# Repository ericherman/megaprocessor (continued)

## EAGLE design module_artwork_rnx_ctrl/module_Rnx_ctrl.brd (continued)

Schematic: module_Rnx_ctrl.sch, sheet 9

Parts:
CMP26, CMP27: 2OR
CMP28: 3AND
CMP29, CMP30: 3OR
CMP48, CMP49: 1BUF

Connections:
ADDER_X_MUX_R0: CMP26.OUT_P, CMP30.P$1 (0); also elsewhere on the board
ADDER_X_MUX_R1: CMP27.OUT_P, CMP30.P$2 (1); also elsewhere on the board
ADDER_X_MUX_R1__DIV: CMP27.P$1 (A2); also elsewhere on the board
ADDER_X_MUX_R3: CMP29.OUT_P, CMP30.P$3 (2); also elsewhere on the board
ADDER_X_MUX_R3_SET_A: CMP28.OUT_P, CMP29.P$1 (0)
ADDER_X_MUX_SPECIAL: CMP30.OUT_P; also elsewhere on the board
ADDER_X_MUX_SPECIAL_N: CMP30.OUT_M (N)
OPCODE_IS_ADDX: CMP26.P$2 (A1); also elsewhere on the board
OPCODE_IS_MUL: CMP28.P$3 (3); also elsewhere on the board
OPCODE_IS_SQRT: CMP27.P$2 (A1); also elsewhere on the board
OPCODE_IS_SUBX: CMP26.P$1 (A2); also elsewhere on the board
STATE_0: CMP48.IN; also elsewhere on the board
STATE_0_N: CMP28.P$2 (2), CMP48.N; also elsewhere on the board
STATE_11: CMP29.P$2 (1); also elsewhere on the board
STATE_13: CMP29.P$3 (2), CMP49.IN; also elsewhere on the board
STATE_13_N: CMP28.P$1 (1), CMP49.N

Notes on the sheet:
adder_x_mux_r0 = Cpnt_2OR(bus_decode_rnx_2.opcode_is_addx, bus_decode_rnx_2.opcode_is_subx);
adder_x_mux_r1 = Cpnt_2OR(bus_decode_rnx_1.opcode_is_sqrt, adder_x_mux_r1__div);
adder_x_mux_r3_A = Cpnt_3AND(bus_decode_rnx_1.opcode_is_mul, ~bus_state[0], ~bus_state[13]);
adder_x_mux_r3 = Cpnt_3OR(bus_state[11], bus_state[13],adder_x_mux_r3_A);
adder_x_special = Cpnt_3OR(adder_x_mux_r0, adder_x_mux_r1, adder_x_mux_r3);

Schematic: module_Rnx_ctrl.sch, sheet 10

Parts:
CMP32, CMP37: 2OR
CMP33, CMP34: 2AND
CMP35, CMP36: 3OR

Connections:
ADDER_X_MUX_R0: CMP35.P$1 (0); also elsewhere on the board
ADDER_X_MUX_R1: CMP36.P$1 (0); also elsewhere on the board
ADDER_X_MUX_R3: CMP37.P$1 (A2); also elsewhere on the board
ADDER_X_MUX_SPECIAL: CMP32.P$1 (A2); also elsewhere on the board
INSTR_0: CMP34.P$1 (1); also elsewhere on the board
INSTR_0_N: CMP33.P$1 (1); also elsewhere on the board
OPCODE_IS_INDIRECT_POSTINC: CMP32.P$2 (A1), CMP33.P$2 (2), CMP34.P$2 (2); also elsewhere on the board
RAC_MUX_0: CMP35.OUT_P; also elsewhere on the board
RAC_MUX_1: CMP36.OUT_P; also elsewhere on the board
RAC_MUX_3: CMP37.OUT_P; also elsewhere on the board
RA_MUX_0_RC: CMP33.OUT_P, CMP35.P$2 (1)
RA_MUX_1_RC: CMP34.OUT_P, CMP36.P$2 (1)
RA_MUX_NORM_EN: CMP32.OUT_M (N); also elsewhere on the board
RA_NORM_0: CMP35.P$3 (2); also elsewhere on the board
RA_NORM_1: CMP36.P$3 (2); also elsewhere on the board
RA_NORM_3: CMP37.P$2 (A1); also elsewhere on the board

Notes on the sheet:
RAC_mux_0 = Cpnt_3OR(adder_x_mux_r0, RA_mux_0__norm, RA_mux_0__RC);
RAC_mux_1 = Cpnt_3OR(adder_x_mux_r1, RA_mux_1__norm, RA_mux_1__RC);
RAC_mux_2 = RA_mux_2__norm;
RAC_mux_3 = Cpnt_2OR(adder_x_mux_r3, RA_mux_3__norm);
RA_mux_0__RC = Cpnt_2AND(bus_decode_rnx_2.opcode_is_indirect_postinc, ~RC_bit);
RA_mux_1__RC = Cpnt_2AND(bus_decode_rnx_2.opcode_is_indirect_postinc, RC_bit);
RA_mux_norm_en = ~Cpnt_2OR(adder_x_special, bus_decode_rnx_2.opcode_is_indirect_postinc);

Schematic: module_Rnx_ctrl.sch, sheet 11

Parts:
CMP20, CMP80: 2X2AND_OR
CMP22: 2AND
CMP82: 5OR

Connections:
INSTR_7_N: CMP22.P$1 (1); also elsewhere on the board
OPCODE_IS_LDI_X: CMP20.P$2 (A1), CMP20.P$3 (B0); also elsewhere on the board
OPCODE_IS_LD_ST: CMP80.P$1 (A0), CMP80.P$3 (B0); also elsewhere on the board
SHIFT_IS_SHIFTING: CMP82.3 (2); also elsewhere on the board
STATE_0: CMP20.P$4 (B1); also elsewhere on the board
STATE_1: CMP20.P$1 (A0); also elsewhere on the board
STATE_4: CMP80.P$4 (B1); also elsewhere on the board
STATE_5: CMP80.P$2 (A1); also elsewhere on the board
WR_RN_USING_RAC: CMP82.OUT_P; also elsewhere on the board
WR_RN_USING_RAC__MEM: CMP80.OUT_P, CMP82.4 (3)
WR_RN_USING_RA__BIT: CMP82.2 (1); also elsewhere on the board
WR_RN_USING_RA__LDI: CMP20.OUT_P, CMP82.1 (0)
WR_RN_USING_RA__REG_REG: CMP22.OUT_P, CMP82.5 (4)
WR_RN_USING_RA__REG_REG_EXCEPTIONS_N: CMP22.P$2 (2); also elsewhere on the board

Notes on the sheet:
wr_RN_using_ra__ldi = Cpnt_2x2AND_OR( bus_state[0], bus_decode_rnx_1.opcode_is_ldi_x, bus_state[1], bus_decode_rnx_1.opcode_is_ldi_x);
wr_RN_using_ra__reg_reg = Cpnt_2AND(is_simple_reg_to_reg, bus_decode_rnx_1.wr_RN_using_ra__reg_reg_exceptions_n);
wr_RN_using_rac__mem = Cpnt_2x2AND_OR(bus_state[4], bus_decode_rnx_1.opcode_is_ld_st, bus_state[5], bus_decode_rnx_1.opcode_is_ld_st);
wr_RN_using_rac = Cpnt_5OR( wr_RN_using_ra__reg_reg, wr_RN_using_rac__mem, bus_decode_rnx_1.wr_RN_using_ra__bit, wr_RN_using_ra__ldi, bus_decode_rnx_1.shift_is_shifting);

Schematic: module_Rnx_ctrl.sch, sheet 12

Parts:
CMP2: 2X2AND_OR
CMP3, CMP4: 4OR
CMP6, CMP7: 2OR

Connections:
ADDER_Y_MUX_R0: CMP2.OUT_P, CMP4.4 (3); also elsewhere on the board
ADDER_Y_MUX_R1: CMP3.OUT_P, CMP4.2 (1); also elsewhere on the board
ADDER_Y_MUX_R2__DIV: CMP4.1 (0); also elsewhere on the board
ADDER_Y_MUX_R3: CMP4.3 (2), CMP6.OUT_P; also elsewhere on the board
ADDER_Y_MUX_SPECIAL: CMP4.OUT_P, CMP7.P$1 (A2); also elsewhere on the board
ADDER_Y_MUX_SPECIAL_N: CMP4.OUT_M (N)
OPCODE_IS_ADDX: CMP3.1 (0); also elsewhere on the board
OPCODE_IS_DIVS_STATE_0: CMP3.3 (2); also elsewhere on the board
OPCODE_IS_MULS: CMP2.P$2 (A1); also elsewhere on the board
OPCODE_IS_NEGX: CMP2.P$3 (B0), CMP2.P$4 (B1); also elsewhere on the board
OPCODE_IS_SHIFT_BIT: CMP7.P$2 (A1); also elsewhere on the board
OPCODE_IS_SQRT: CMP6.P$2 (A1); also elsewhere on the board
OPCODE_IS_SUBX: CMP3.2 (1); also elsewhere on the board
RB_MUX_NORM_EN: CMP7.OUT_M (N); also elsewhere on the board
STATE_3: CMP2.P$1 (A0); also elsewhere on the board
STATE_11: CMP3.4 (3); also elsewhere on the board
STATE_12: CMP6.P$1 (A2); also elsewhere on the board

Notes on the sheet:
adder_y_mux_r0 = Cpnt_2x2AND_OR( bus_decode_rnx_2.opcode_is_negx, bus_decode_rnx_2.opcode_is_negx, bus_decode_rnx_2.opcode_is_muls, bus_state[3]);
adder_y_mux_r1 = Cpnt_4OR(bus_decode_rnx_2.opcode_is_addx, bus_decode_rnx_2.opcode_is_subx, adder_y_mux_r1__div, bus_state[11]);
adder_y_mux_r2 = adder_y_mux_r2__div;
adder_y_mux_r3 = Cpnt_2OR(bus_decode_rnx_1.opcode_is_sqrt, adder_y_mux_r3__div);
adder_y_special = Cpnt_4OR(adder_y_mux_r0, adder_y_mux_r1, adder_y_mux_r2, adder_y_mux_r3);
RB_mux_norm_en = ~Cpnt_2OR(adder_y_special, bus_decode_rnx_2.opcode_is_shift_bit);

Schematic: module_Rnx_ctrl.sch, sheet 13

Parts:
CMP8, CMP12, CMP14, CMP19: 3OR

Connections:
ADDER_Y_MUX_R0: CMP8.P$3 (2); also elsewhere on the board
ADDER_Y_MUX_R1: CMP12.P$2 (1); also elsewhere on the board
ADDER_Y_MUX_R2__DIV: CMP14.P$1 (0); also elsewhere on the board
ADDER_Y_MUX_R3: CMP19.P$1 (0); also elsewhere on the board
RB_MUX_0: CMP8.OUT_P; also elsewhere on the board
RB_MUX_1: CMP12.OUT_P; also elsewhere on the board
RB_MUX_2: CMP14.OUT_P; also elsewhere on the board
RB_MUX_3: CMP19.OUT_P; also elsewhere on the board
RB_NORM_0: CMP8.P$1 (0); also elsewhere on the board
RB_NORM_1: CMP12.P$1 (0); also elsewhere on the board
RB_NORM_2: CMP14.P$3 (2); also elsewhere on the board
RB_NORM_3: CMP19.P$2 (1); also elsewhere on the board
RB_SHIFT_0: CMP8.P$2 (1); also elsewhere on the board
RB_SHIFT_1: CMP12.P$3 (2); also elsewhere on the board
RB_SHIFT_2: CMP14.P$2 (1); also elsewhere on the board
RB_SHIFT_3: CMP19.P$3 (2); also elsewhere on the board

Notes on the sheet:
RB_mux_0 = Cpnt_3OR(adder_y_mux_r0, RB_mux_0__shift, RB_mux_0__norm);
RB_mux_1 = Cpnt_3OR(adder_y_mux_r1, RB_mux_1__shift, RB_mux_1__norm);
RB_mux_2 = Cpnt_3OR(adder_y_mux_r2, RB_mux_2__shift, RB_mux_2__norm);
RB_mux_3 = Cpnt_3OR(adder_y_mux_r3, RB_mux_3__shift, RB_mux_3__norm);

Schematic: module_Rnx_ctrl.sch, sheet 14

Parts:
CMP55: 1BUF
CMP58, CMP59: 2X2AND_OR
CMP60: 4AND
CMP61: 5OR
CMP85: 3AND

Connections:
ADD2_X_MUX_RI_SP__STACK_SET_A: CMP59.OUT_P
ADD2_X_MUX_RI_SP__STACK_SET_A_N: CMP59.OUT_M (N), CMP60.P$4 (3)
ADD2_X_MUX_RI__H: CMP85.OUT_P; also elsewhere on the board
ADD2_X_MUX_RI__SP: CMP61.OUT_P; also elsewhere on the board
ADD2_X_MUX_RI__SP__JSR_ABS: CMP58.OUT_P, CMP61.4 (3); also elsewhere on the board
ADD2_X_MUX_RI__SP__STACK: CMP60.OUT_P, CMP61.5 (4)
INSTR_6_N: CMP85.P$3 (3); also elsewhere on the board
INSTR_7: CMP85.P$2 (2); also elsewhere on the board
IS_END_N: CMP60.P$2 (1); also elsewhere on the board
IS_STATE_4_6: CMP85.P$1 (1); also elsewhere on the board
OPCODE_IS_ADD_SP_STATE_2: CMP61.1 (0); also elsewhere on the board
OPCODE_IS_JSR_ABS: CMP55.IN, CMP58.P$2 (A1), CMP58.P$4 (B1); also elsewhere on the board
OPCODE_IS_JSR_ABS_N: CMP55.N, CMP60.P$3 (2)
OPCODE_IS_JSR_R0: CMP59.P$4 (B1); also elsewhere on the board
OPCODE_IS_MOVE_R0_SP_STATE_0: CMP61.2 (1); also elsewhere on the board
OPCODE_IS_STACK_GROUP: CMP60.P$1 (0); also elsewhere on the board
OPCODE_IS_STACK_REL_STATE_2: CMP61.3 (2); also elsewhere on the board
OPCODE_IS_TRAP: CMP59.P$2 (A1); also elsewhere on the board
STATE_0: CMP59.P$1 (A0); also elsewhere on the board
STATE_6: CMP58.P$1 (A0); also elsewhere on the board
STATE_7: CMP59.P$3 (B0); also elsewhere on the board
STATE_15: CMP58.P$3 (B0); also elsewhere on the board

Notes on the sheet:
add2_x_mux_ri__h = Cpnt_3AND(bus_f_instr.instr[7], ~bus_f_instr.instr[6], is_state_4_6);
add2_x_mux_ri__sp__jsr_abs = Cpnt_2x2AND_OR(bus_decode_rnx_2.opcode_is_jsr_abs, bus_state[15], bus_decode_rnx_2.opcode_is_jsr_abs, bus_state[6]);
add2_x_mux_ri__sp__stack_set_A = Cpnt_2x2AND_OR(bus_decode_rnx_2.opcode_is_jsr_r0, bus_state[7], bus_state[0], bus_decode_rnx_2.opcode_is_trap);
add2_x_mux_ri__sp__stack = Cpnt_4AND(bus_decode_rnx_2.opcode_is_stack_group, bus_decode_rnx_2.is_end_n, ~bus_decode_rnx_2.opcode_is_jsr_abs, ~add2_x_mux_ri__sp__stack_set_A);
add2_x_mux_ri__sp = Cpnt_5OR(bus_decode_rnx_2.opcode_is_stack_rel_state_2, bus_decode_rnx_2.opcode_is_add_sp_state_2, bus_decode_rnx_1.opcode_is_move_r0_sp_state_0, add2_x_mux_ri__sp__stack, add2_x_mux_ri__sp__jsr_abs);

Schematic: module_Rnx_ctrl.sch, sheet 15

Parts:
CMP1, CMP41, CMP62: 2OR
CMP43: 3OR
CMP45, CMP64: 2X2AND_OR

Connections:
ADD2_X_MUX_RI__H: CMP41.P$1 (A2); also elsewhere on the board
ADD2_X_MUX_RI__SP: CMP43.P$1 (0); also elsewhere on the board
ALL_POPS: CMP64.P$2 (A1); also elsewhere on the board
INSTR_1_N: CMP45.P$2 (A1); also elsewhere on the board
IS_STATE_0_4: CMP62.OUT_P, CMP64.P$1 (A0)
NEXT_ADDR_MUX_RI__SP: CMP64.OUT_P; also elsewhere on the board
RI_MUX_2_QUAL: CMP45.OUT_P; also elsewhere on the board
RI_MUX_H: CMP41.OUT_P, CMP43.P$2 (1); also elsewhere on the board
RI_MUX_R2: CMP1.OUT_P, CMP43.P$3 (2), CMP45.P$3 (B0), CMP45.P$4 (B1)
RI_MUX_SPECIAL: CMP43.OUT_P
RI_MUX_SPECIAL_N: CMP43.OUT_M (N), CMP45.P$1 (A0); also elsewhere on the board
STATE_0: CMP62.P$1 (A2); also elsewhere on the board
STATE_4: CMP62.P$2 (A1); also elsewhere on the board
STATE_8: CMP64.P$3 (B0), CMP64.P$4 (B1); also elsewhere on the board
STATE_11: CMP1.P$1 (A2); also elsewhere on the board
STATE_12: CMP1.P$2 (A1); also elsewhere on the board
STATE_14: CMP41.P$2 (A1); also elsewhere on the board

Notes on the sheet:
is_state_0_4 = Cpnt_2OR(bus_state[0], bus_state[4]);
next_addr_mux_ri__sp_set_A = bus_decode_rnx_2.all_pops;
next_addr_mux_ri__sp = Cpnt_2x2AND_OR(bus_state[8], bus_state[8], next_addr_mux_ri__sp_set_A, is_state_0_4);
RI_mux_h = Cpnt_2OR(add2_x_mux_ri__h, bus_state[14]);
RI_mux_sp = add2_x_mux_ri__sp;// superset | next_addr_mux_ri__sp;
RI_mux_r2 = Cpnt_2OR(bus_state[11],bus_state[12]);//,bus_state[13]);
RI_mux_special = Cpnt_3OR( RI_mux_h, RI_mux_sp, RI_mux_r2);
RI_mux_2 = ~RI_bit; RI_mux_3 = RI_bit;
RI_mux_2_qual = Cpnt_2x2AND_OR(RI_mux_2, ~RI_mux_special, RI_mux_r2, RI_mux_r2);

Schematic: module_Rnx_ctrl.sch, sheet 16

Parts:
CMP5: 2X2AND_OR
CMP13: 5OR
CMP15: 2OR
CMP16, CMP17, CMP46: 2AND
CMP50: 2X3AND_OR
CMP83: 1BUF

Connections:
DIR_SZ_IS_LOAD_BYTE: CMP16.P$2 (2); also elsewhere on the board
DIR_SZ_IS_LOAD_WORD: CMP17.P$2 (2); also elsewhere on the board
INSTR_1: CMP46.P$1 (1); also elsewhere on the board
INSTR_2: CMP50.P$5 (B1); also elsewhere on the board
INSTR_2_N: CMP50.P$2 (A1); also elsewhere on the board
INSTR_7_N: CMP5.P$4 (B1); also elsewhere on the board
IS_STATE_4_6: CMP50.P$1 (A0); also elsewhere on the board
MAIN_RN_INPUT_MUX_0XT_READ: CMP15.OUT_P; also elsewhere on the board
MAIN_RN_INPUT_MUX_0XT_READ__LOAD_BYTE: CMP15.P$2 (A1), CMP16.OUT_P
MAIN_RN_INPUT_MUX_ALU: CMP13.OUT_P; also elsewhere on the board
MAIN_RN_INPUT_MUX_ALU__SET_A: CMP5.OUT_P, CMP13.5 (4)
MAIN_RN_INPUT_MUX_SHIFT_RAC: CMP17.OUT_P; also elsewhere on the board
OPCODE_IS_DIV: CMP13.3 (2); also elsewhere on the board
OPCODE_IS_LD_ST: CMP16.P$1 (1), CMP17.P$1 (1); also elsewhere on the board
OPCODE_IS_MUL: CMP5.P$2 (A1); also elsewhere on the board
OPCODE_IS_POP_PS: CMP15.P$1 (A2); also elsewhere on the board
OPCODE_IS_POSTINC_GROUP: CMP50.P$3 (A2), CMP50.P$4 (B0); also elsewhere on the board
OPCODE_IS_SHIFT_BIT: CMP13.2 (1); also elsewhere on the board
OPCODE_IS_SQRT: CMP13.1 (0); also elsewhere on the board
OPCODE_IS_SXT: CMP83.IN; also elsewhere on the board
OPCODE_IS_SXT_N: CMP5.P$3 (B0), CMP83.N
OPCODE_IS_X_ARITH: CMP13.4 (3); also elsewhere on the board
RI_MUX_3_QUAL: CMP46.OUT_P; also elsewhere on the board
RI_MUX_SPECIAL_N: CMP46.P$2 (2); also elsewhere on the board
STATE_0: CMP50.P$6 (B2); also elsewhere on the board
STATE_0_N: CMP5.P$1 (A0); also elsewhere on the board
WR_RN_USING_RI: CMP50.OUT_P; also elsewhere on the board

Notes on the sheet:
RI_mux_3_qual = Cpnt_2AND(RI_mux_3, ~RI_mux_special);
wr_RN_using_ri = Cpnt_2x3AND_OR(bus_decode_rnx_1.opcode_is_postinc_group, size_bit_is_byte, bus_state[0], bus_decode_rnx_1.opcode_is_postinc_group, ~size_bit_is_byte, is_state_4_6);
main_rn_input_mux_sxt = bus_decode_rnx_1.opcode_is_sxt;
main_rn_input_mux_alu__set_A = Cpnt_2x2AND_OR(is_simple_reg_to_reg, ~bus_decode_rnx_1.opcode_is_sxt, bus_decode_rnx_1.opcode_is_mul, ~bus_state[0]);
main_rn_input_mux_alu = Cpnt_5OR(main_rn_input_mux_alu__set_A, bus_decode_rnx_1.opcode_is_x_arith, bus_decode_rnx_2.opcode_is_shift_bit, bus_decode_rnx_1.opcode_is_sqrt, bus_decode_rnx_2.opcode_is_div);
main_rn_input_mux_0xt_read__load_byte = Cpnt_2AND(dir_sz_is_load_byte, bus_decode_rnx_1.opcode_is_ld_st);
main_rn_input_mux_0xt_read = Cpnt_2OR(main_rn_input_mux_0xt_read__load_byte, bus_decode_rnx_1.opcode_is_pop_ps);
main_rn_input_mux_shift_rac__mem_subgroup = bus_decode_rnx_1.opcode_is_ld_st;
main_rn_input_mux_shift_rac = Cpnt_2AND(dir_sz_is_load_word, main_rn_input_mux_shift_rac__mem_subgroup);

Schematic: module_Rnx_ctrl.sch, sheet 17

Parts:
CMP63, CMP74: 2OR
CMP72: 3AND
CMP91: 1BUF

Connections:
ADD1_RESULT_IS_N: CMP91.IN; also elsewhere on the board
ADD1_RESULT_IS_P: CMP63.P$1 (A2), CMP91.N
H_0: CMP72.P$2 (2); also elsewhere on the board
R1_IS_N: CMP63.P$2 (A1); also elsewhere on the board
SQRT_CONDITIONAL: CMP63.OUT_P, CMP72.P$1 (1)
SQRT_ODD_CONDITIONAL: CMP72.OUT_P, CMP74.P$2 (A1); also elsewhere on the board
SQRT_ODD_CONDITIONAL_MUL_14: CMP74.OUT_P; also elsewhere on the board
STATE_10: CMP72.P$3 (3); also elsewhere on the board
STATE_14: CMP74.P$1 (A2); also elsewhere on the board

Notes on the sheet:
sqrt_conditional = Cpnt_2OR(~bus_alu_flags.add1_result_is_n, bus_rn_arith_flags.r1_is_n); // if top bit of reg1 set then must be ok
sqrt_odd_conditional = Cpnt_3AND(bus_state[10], bus_H[0], sqrt_conditional);
sqrt_odd_conditional_mul_14 = Cpnt_2OR(sqrt_odd_conditional, bus_state[14]);

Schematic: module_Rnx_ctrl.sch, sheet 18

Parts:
CMP9: 4OR
CMP42, CMP54, CMP69: 2AND
CMP44, CMP68: 3OR
CMP56: 2X2AND_OR

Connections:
LOAD_WEIGHT: CMP42.P$1 (1), CMP54.P$2 (2); also elsewhere on the board
NEXT_R0_MUX_ADD2: CMP9.2 (1), CMP44.OUT_P; also elsewhere on the board
NEXT_R0_MUX_ADD2__WEIGHT: CMP42.OUT_P, CMP44.P$2 (1)
NEXT_R0_MUX_HOLD: CMP9.OUT_M (N); also elsewhere on the board
NEXT_R0_MUX_MAIN: CMP9.3 (2), CMP56.OUT_P; also elsewhere on the board
NEXT_R1_MUX_ADD2: CMP54.OUT_P; also elsewhere on the board
NEXT_R1_MUX_MAIN: CMP68.OUT_P; also elsewhere on the board
NEXT_R1_MUX_MAIN__DIV: CMP68.P$1 (0); also elsewhere on the board
NEXT_R1_MUX_MAIN__RAC: CMP68.P$2 (1), CMP69.OUT_P
OPCODE_IS_MOVE_R0_SP_STATE_0: CMP44.P$3 (2); also elsewhere on the board
OPCODE_IS_X_ARITH: CMP56.P$1 (A0), CMP56.P$2 (A1); also elsewhere on the board
RAC_MUX_0: CMP42.P$2 (2), CMP56.P$4 (B1); also elsewhere on the board
RAC_MUX_1: CMP54.P$1 (1), CMP69.P$1 (1); also elsewhere on the board
SQRT_ODD_CONDITIONAL: CMP68.P$3 (2); also elsewhere on the board
SQRT_ODD_CONDITIONAL_MUL_14: CMP44.P$1 (0); also elsewhere on the board
SQRT_STATE_0: CMP9.4 (3); also elsewhere on the board
SQRT_STATE_10_EVEN_CYCLE: CMP9.1 (0); also elsewhere on the board
WR_RN_USING_RAC: CMP56.P$3 (B0), CMP69.P$2 (2); also elsewhere on the board

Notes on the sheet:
next_r0_mux_main = Cpnt_2x2AND_OR(wr_RN_using_rac, RAC_mux_0, bus_decode_rnx_1.opcode_is_x_arith,bus_decode_rnx_1.opcode_is_x_arith);
next_r0_mux_shift_1 = sqrt_state_10_even_cycle;
next_r0_mux_add2__weight = Cpnt_2AND( RAC_mux_0,bus_decode_rnx_1.load_weight);
next_r0_mux_add2 = Cpnt_3OR(sqrt_odd_conditional_mul_14, bus_decode_rnx_1.opcode_is_move_r0_sp_state_0,next_r0_mux_add2__weight);
// next_r0_mux_clear = sqrt_state_0; next_r0_mux_hold = ~Cpnt_4OR(next_r0_mux_main, next_r0_mux_shift_1, next_r0_mux_add2, sqrt_state_0);
next_r1_mux_main__RAC = Cpnt_2AND(wr_RN_using_rac, RAC_mux_1);
next_r1_mux_main = Cpnt_3OR(next_r1_mux_main__RAC, sqrt_odd_conditional, next_r1_mux_main__div);
//next_r1_mux_mul = bus_state[13];
next_r1_mux_add2 = Cpnt_2AND( RAC_mux_1,bus_decode_rnx_1.load_weight);

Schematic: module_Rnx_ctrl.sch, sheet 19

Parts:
CMP40: 3OR
CMP66: 2OR
CMP70: 2X2AND_OR
CMP73: 2AND
CMP81: 4X2AND_OR

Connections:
DIV_BY_ZERO_N: CMP81.P$3 (B0); also elsewhere on the board
DIV_DIFF_SIGN: CMP70.P$1 (A0); also elsewhere on the board
DIV_SGN_STATE12_NZ_REM: CMP81.P$5 (C0); also elsewhere on the board
FLAG_D: CMP81.P$6 (C1); also elsewhere on the board
INSTR_1_N: CMP81.P$8 (D1); also elsewhere on the board
LOAD_WEIGHT: CMP81.P$2 (A1); also elsewhere on the board
NEXT_R1_MUX_ADD2: CMP40.P$2 (1); also elsewhere on the board
NEXT_R1_MUX_HOLD: CMP40.OUT_M (N); also elsewhere on the board
NEXT_R1_MUX_MAIN: CMP40.P$3 (2); also elsewhere on the board
NEXT_R2_MUX_ADD2: CMP66.OUT_P; also elsewhere on the board
NEXT_R2_MUX_ADD2__A: CMP66.P$1 (A2), CMP81.OUT_P
NEXT_R2_MUX_CLEAR: CMP73.OUT_P; also elsewhere on the board
NEXT_R2_MUX_MAIN: CMP70.OUT_P; also elsewhere on the board
OPCODE_IS_DIV_STATE_0: CMP81.P$4 (B1); also elsewhere on the board
OPCODE_IS_MUL: CMP73.P$1 (1); also elsewhere on the board
RA_NORM_2: CMP70.P$3 (B0), CMP81.P$1 (A0); also elsewhere on the board
STATE_0: CMP73.P$2 (2); also elsewhere on the board
STATE_3: CMP70.P$2 (A1); also elsewhere on the board
STATE_13: CMP40.P$1 (0), CMP66.P$2 (A1); also elsewhere on the board
WR_RN_USING_RAC: CMP70.P$4 (B1); also elsewhere on the board
WR_RN_USING_RI: CMP81.P$7 (D0); also elsewhere on the board

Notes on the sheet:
next_r1_mux_hold = ~Cpnt_3OR(next_r1_mux_main, bus_state[13],next_r1_mux_add2);
next_r2_mux_main = Cpnt_2x2AND_OR(wr_RN_using_rac, RAC_mux_2, bus_state[3], bus_decode_rnx_1.div_diff_sign);
next_r2_mux_clear = Cpnt_2AND(bus_decode_rnx_1.opcode_is_mul, bus_state[0]);
next_r2_mux_add2__A = Cpnt_4x2AND_OR(RAC_mux_2,bus_decode_rnx_1.load_weight, div_sgn_state12_nz_rem, bus_PS[WiC_PS_FLAG_INDEX_D], wr_RN_using_ri , RI_mux_2, bus_decode_rnx_1.opcode_is_div_state_0, bus_decode_rnx_1.div_by_zero_n);
next_r2_mux_add2 = Cpnt_2OR(bus_state[13],next_r2_mux_add2__A);

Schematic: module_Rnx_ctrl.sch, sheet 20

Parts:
CMP10: 4OR
CMP75: 2X2AND_OR
CMP78, CMP79: 4X2AND_OR
CMP92: 1BUF

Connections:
ARITH_C: CMP92.IN; also elsewhere on the board
ARITH_C_N: CMP78.P$1 (A0), CMP92.N; also elsewhere on the board
DIV_BY_ZERO_N: CMP79.P$5 (C0); also elsewhere on the board
DIV_SGN_STATE12_NZ_REM: CMP78.P$3 (B0), CMP78.P$4 (B1); also elsewhere on the board
INSTR_1: CMP75.P$3 (B0); also elsewhere on the board
LOAD_WEIGHT: CMP75.P$2 (A1); also elsewhere on the board
unnamed: CMP79.P$1 (A0), CMP79.P$2 (A1)
NEXT_R2_MUX_ADD2: CMP10.3 (2); also elsewhere on the board
NEXT_R2_MUX_CLEAR: CMP10.2 (1); also elsewhere on the board
NEXT_R2_MUX_HOLD: CMP10.OUT_M (N); also elsewhere on the board
NEXT_R2_MUX_MAIN: CMP10.4 (3); also elsewhere on the board
NEXT_R3_MUX_ADD2__A: CMP75.OUT_P; also elsewhere on the board
NEXT_R3_MUX_CLEAR: CMP79.OUT_P; also elsewhere on the board
NEXT_R3_MUX_MAIN: CMP78.OUT_P; also elsewhere on the board
OPCODE_IS_DIV_STATE_0: CMP79.P$6 (C1); also elsewhere on the board
OPCODE_IS_MUL: CMP78.P$6 (C1), CMP79.P$8 (D1); also elsewhere on the board
OPCODE_IS_SQRT: CMP79.P$3 (B0); also elsewhere on the board
RAC_MUX_3: CMP75.P$1 (A0), CMP78.P$7 (D0); also elsewhere on the board
STATE_0: CMP79.P$7 (D0); also elsewhere on the board
STATE_0_N: CMP78.P$5 (C0); also elsewhere on the board
STATE_3: CMP79.P$4 (B1); also elsewhere on the board
STATE_11: CMP10.1 (0), CMP78.P$2 (A1); also elsewhere on the board
WR_RN_USING_RAC: CMP78.P$8 (D1); also elsewhere on the board
WR_RN_USING_RI: CMP75.P$4 (B1); also elsewhere on the board

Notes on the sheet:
next_r2_mux_hold = ~Cpnt_4OR(next_r2_mux_main, next_r2_mux_add2, next_r2_mux_clear, next_r2_mux_div_shift);
next_r3_mux_main = Cpnt_4x2AND_OR(wr_RN_using_rac, RAC_mux_3, bus_decode_rnx_1.opcode_is_mul, ~bus_state[0], div_sgn_state12_nz_rem,div_sgn_state12_nz_rem, // division bus_state[11], ~bus_alu_flags.arith_C);
next_r3_mux_clear = Cpnt_4x2AND_OR(bus_decode_rnx_1.opcode_is_mul, bus_state[0], bus_decode_rnx_1.opcode_is_div_state_0, bus_decode_rnx_1.div_by_zero_n, bus_decode_rnx_1.opcode_is_sqrt, bus_state[3], // clear at end of sqrt for simulation BIT_VAL_0,BIT_VAL_0);
next_r3_mux_add2__A = Cpnt_2x2AND_OR( RAC_mux_3,bus_decode_rnx_1.load_weight, wr_RN_using_ri, RI_mux_3);

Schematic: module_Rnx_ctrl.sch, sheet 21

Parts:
CMP24: 4OR
CMP71: 2OR
CMP77, CMP93: 2AND

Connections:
ARITH_C: CMP77.P$1 (1); also elsewhere on the board
ARITH_C_N: CMP93.P$2 (2); also elsewhere on the board
NEXT_R3_MUX_ADD2: CMP24.2 (1), CMP71.OUT_P; also elsewhere on the board
NEXT_R3_MUX_ADD2__A: CMP71.P$1 (A2); also elsewhere on the board
NEXT_R3_MUX_CLEAR: CMP24.1 (0); also elsewhere on the board
NEXT_R3_MUX_DIV_SHIFT_R3: CMP24.4 (3), CMP77.OUT_P; also elsewhere on the board
NEXT_R3_MUX_HOLD: CMP24.OUT_M (N); also elsewhere on the board
NEXT_R3_MUX_MAIN: CMP24.3 (2); also elsewhere on the board
R2_SHIFT_IN: CMP93.OUT_P; also elsewhere on the board
SQRT_STATE_10_EVEN_CYCLE: CMP71.P$2 (A1); also elsewhere on the board
STATE_11: CMP77.P$2 (2), CMP93.P$1 (1); also elsewhere on the board

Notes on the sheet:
next_r3_mux_add2 = Cpnt_2OR(sqrt_state_10_even_cycle, next_r3_mux_add2__A);
next_r3_mux_div_shift_r3 = Cpnt_2AND(bus_state[11], bus_alu_flags.arith_C);
next_r3_mux_hold = ~Cpnt_4OR(next_r3_mux_main, next_r3_mux_clear, next_r3_mux_add2, next_r3_mux_div_shift_r3);

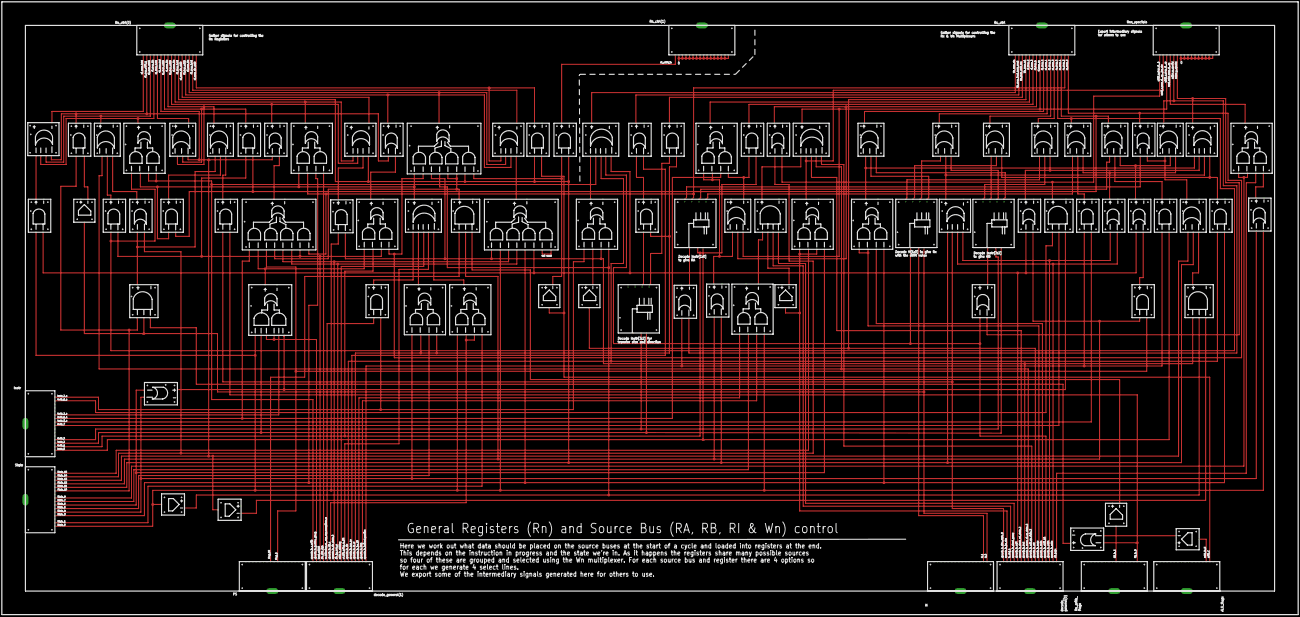
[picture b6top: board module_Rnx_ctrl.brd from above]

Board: 2 copper layers, 1397.0 x 660.4 mm, 96 parts (0 on the bottom side), 161 nets.

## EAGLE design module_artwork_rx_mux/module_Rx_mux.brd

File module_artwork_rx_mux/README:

Rx Mux

This multiplexes R0:R3 to generate three buses (RA, RB and RI) that act
as sources for operations. It also multiplexes several buses to generate
the Wn bus that may be used as one of the results that can be written
into the R0:R3 registers.

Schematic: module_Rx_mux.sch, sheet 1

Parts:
CMP1: BUS_SPLIT_DISPLAY

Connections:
MAIN_RN_INPUT_MUX_0XT_READ: CMP1.P$2 (OUT_1); also elsewhere on the board
MAIN_RN_INPUT_MUX_ALU: CMP1.P$1 (OUT_0); also elsewhere on the board
MAIN_RN_INPUT_MUX_SHIFT_RAC: CMP1.P$3 (OUT_2); also elsewhere on the board
MAIN_RN_INPUT_MUX_SXT: CMP1.P$4 (OUT_3); also elsewhere on the board
RAC_MUX_0: CMP1.P$13 (OUT_12); also elsewhere on the board
RAC_MUX_1: CMP1.P$14 (OUT_13); also elsewhere on the board
RAC_MUX_2: CMP1.P$15 (OUT_14); also elsewhere on the board
RAC_MUX_3: CMP1.P$16 (OUT_15); also elsewhere on the board
RB_MUX_0: CMP1.P$9 (OUT_8); also elsewhere on the board
RB_MUX_1: CMP1.P$10 (OUT_9); also elsewhere on the board
RB_MUX_2: CMP1.P$11 (OUT_10); also elsewhere on the board
RB_MUX_3: CMP1.P$12 (OUT_11); also elsewhere on the board
RI_MUX_2: CMP1.P$5 (OUT_4); also elsewhere on the board
RI_MUX_3: CMP1.P$6 (OUT_5); also elsewhere on the board
RI_MUX_H: CMP1.P$7 (OUT_6); also elsewhere on the board
RI_MUX_SP: CMP1.P$8 (OUT_7); also elsewhere on the board

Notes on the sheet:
clBit main_rn_input_mux_alu; // 0 clBit main_rn_input_mux_0xt_read; // 1 clBit main_rn_input_mux_shift_rac; // 2 clBit main_rn_input_mux_sxt; // 3 clBit RI_mux_2; // 4 clBit RI_mux_3; // 5 clBit RI_mux_H; // 6 clBit RI_mux_SP; // 7 clBit RB_mux_0; // 8 clBit RB_mux_1; // 9 clBit RB_mux_2; // 10 clB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

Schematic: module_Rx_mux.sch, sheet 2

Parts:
CMP2, CMP3: BUS_4TEE
CMP6, CMP7, CMP64: BUS_2_BUS; BUS2BUS
CMP8, CMP9: BUS_TEE

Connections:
BUS_ALU1_OUTPUT: CMP64.P$2 (OUT); also elsewhere on the board
BUS_H: CMP6.P$2 (OUT); also elsewhere on the board
BUS_R0: CMP8.INPUT (IN)
BUS_R1: CMP9.INPUT (IN)
BUS_R2: CMP2.SRC
BUS_R3: CMP3.SRC
BUS_SP: CMP7.P$2 (OUT); also elsewhere on the board
R0_A: CMP8.OUT_A (A); also elsewhere on the board
R0_B: CMP8.OUTB (B); also elsewhere on the board
R1_A: CMP9.OUT_A (A); also elsewhere on the board
R1_B: CMP9.OUTB (B); also elsewhere on the board
R2_A: CMP2.1; also elsewhere on the board
R2_B: CMP2.2; also elsewhere on the board
R2_C: CMP2.3; also elsewhere on the board
R3_A: CMP3.1; also elsewhere on the board
R3_B: CMP3.2; also elsewhere on the board
R3_C: CMP3.3; also elsewhere on the board

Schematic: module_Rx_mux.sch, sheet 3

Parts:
CMP17: BUS_2_BUS; BUS2BUS
CMP21, CMP67: BUS_TEE
CMP60, CMP62: BUS_CONSTRUCT_DISPLAY; BUS_SPLIT_DISPLAY
CMP65, CMP66: BUS_SPLIT_DISPLAY

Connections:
BUS_0XT_READ_DATA_A: CMP66.INPUT, CMP67.OUTB (B)
BUS_0XT_READ_DATA_B: CMP67.OUT_A (A); also elsewhere on the board
BUS_RA: CMP21.INPUT (IN); also elsewhere on the board
unnamed: CMP21.OUT_A (A), CMP65.INPUT
unnamed: CMP17.P$1 (IN), CMP21.OUTB (B)
RA_0: CMP62.P$1 (IN_0), CMP65.P$1 (OUT_0)
RA_1: CMP62.P$2 (IN_1), CMP65.P$2 (OUT_1)
RA_2: CMP62.P$3 (IN_2), CMP65.P$3 (OUT_2)
RA_3: CMP62.P$4 (IN_3), CMP65.P$4 (OUT_3)
RA_4: CMP62.P$5 (IN_4), CMP65.P$5 (OUT_4)
RA_5: CMP62.P$6 (IN_5), CMP65.P$6 (OUT_5)
RA_6: CMP62.P$7 (IN_6), CMP65.P$7 (OUT_6)
RA_7: CMP62.P$8 (IN_7), CMP62.P$9 (IN_8), CMP62.P$10 (IN_9), CMP62.P$11 (IN_10), CMP62.P$12 (IN_11), CMP62.P$13 (IN_12), CMP62.P$14 (IN_13), CMP62.P$15 (IN_14), CMP62.P$16 (IN_15), CMP65.P$8 (OUT_7)
RA_8: CMP60.P$1 (IN_0), CMP65.P$9 (OUT_8)
RA_9: CMP60.P$2 (IN_1), CMP65.P$10 (OUT_9)
RA_10: CMP60.P$3 (IN_2), CMP65.P$11 (OUT_10)
RA_11: CMP60.P$4 (IN_3), CMP65.P$12 (OUT_11)
RA_12: CMP60.P$5 (IN_4), CMP65.P$13 (OUT_12)
RA_13: CMP60.P$6 (IN_5), CMP65.P$14 (OUT_13)
RA_14: CMP60.P$7 (IN_6), CMP65.P$15 (OUT_14)
RA_15: CMP60.P$8 (IN_7), CMP65.P$16 (OUT_15)
RD_0: CMP60.P$9 (IN_8), CMP66.P$1 (OUT_0)
RD_1: CMP60.P$10 (IN_9), CMP66.P$2 (OUT_1)
RD_2: CMP60.P$11 (IN_10), CMP66.P$3 (OUT_2)
RD_3: CMP60.P$12 (IN_11), CMP66.P$4 (OUT_3)
RD_4: CMP60.P$13 (IN_12), CMP66.P$5 (OUT_4)
RD_5: CMP60.P$14 (IN_13), CMP66.P$6 (OUT_5)
RD_6: CMP60.P$15 (IN_14), CMP66.P$7 (OUT_6)
RD_7: CMP60.P$16 (IN_15), CMP66.P$8 (OUT_7)
RD_8: CMP66.P$9 (OUT_8)
RD_9: CMP66.P$10 (OUT_9)
RD_10: CMP66.P$11 (OUT_10)
RD_11: CMP66.P$12 (OUT_11)
RD_12: CMP66.P$13 (OUT_12)
RD_13: CMP66.P$14 (OUT_13)
RD_14: CMP66.P$15 (OUT_14)
RD_15: CMP66.P$16 (OUT_15)
READ_DATA_RA: CMP60.INPUT (OUT); also elsewhere on the board
SXT_RA: CMP62.INPUT (OUT); also elsewhere on the board

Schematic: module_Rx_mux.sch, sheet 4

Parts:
CMP14, CMP15, CMP16, CMP69: 4X16MUX
CMP18, CMP19, CMP20: BUS_2_BUS; BUS2BUS

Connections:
BUS_0XT_READ_DATA_B: CMP69.PORT2; also elsewhere on the board
BUS_ALU1_OUTPUT: CMP69.PORT3; also elsewhere on the board
BUS_H: CMP16.PORT1; also elsewhere on the board
BUS_RA: CMP14.PORTOUT (OUTPUT); also elsewhere on the board
BUS_RB: CMP15.PORTOUT (OUTPUT), CMP19.P$1 (IN)
BUS_RI: CMP16.PORTOUT (OUTPUT), CMP20.P$1 (IN)
BUS_SP: CMP16.PORT0; also elsewhere on the board
BUS_WN: CMP18.P$1 (IN), CMP69.PORTOUT (OUTPUT)
MAIN_RN_INPUT_MUX_0XT_READ: CMP69.EN2; also elsewhere on the board
MAIN_RN_INPUT_MUX_ALU: CMP69.EN3; also elsewhere on the board
MAIN_RN_INPUT_MUX_SHIFT_RAC: CMP69.EN1; also elsewhere on the board
MAIN_RN_INPUT_MUX_SXT: CMP69.EN0; also elsewhere on the board
R0_A: CMP14.PORT3; also elsewhere on the board
R0_B: CMP15.PORT3; also elsewhere on the board
R1_A: CMP14.PORT2; also elsewhere on the board
R1_B: CMP15.PORT2; also elsewhere on the board
R2_A: CMP14.PORT1; also elsewhere on the board
R2_B: CMP15.PORT1; also elsewhere on the board
R2_C: CMP16.PORT3; also elsewhere on the board
R3_A: CMP14.PORT0; also elsewhere on the board
R3_B: CMP15.PORT0; also elsewhere on the board
R3_C: CMP16.PORT2; also elsewhere on the board
RAC_MUX_0: CMP14.EN3; also elsewhere on the board
RAC_MUX_1: CMP14.EN2; also elsewhere on the board
RAC_MUX_2: CMP14.EN1; also elsewhere on the board
RAC_MUX_3: CMP14.EN0; also elsewhere on the board
RB_MUX_0: CMP15.EN3; also elsewhere on the board
RB_MUX_1: CMP15.EN2; also elsewhere on the board
RB_MUX_2: CMP15.EN1; also elsewhere on the board
RB_MUX_3: CMP15.EN0; also elsewhere on the board
READ_DATA_RA: CMP69.PORT1; also elsewhere on the board
RI_MUX_2: CMP16.EN3; also elsewhere on the board
RI_MUX_3: CMP16.EN2; also elsewhere on the board
RI_MUX_H: CMP16.EN1; also elsewhere on the board
RI_MUX_SP: CMP16.EN0; also elsewhere on the board
SXT_RA: CMP69.PORT0; also elsewhere on the board

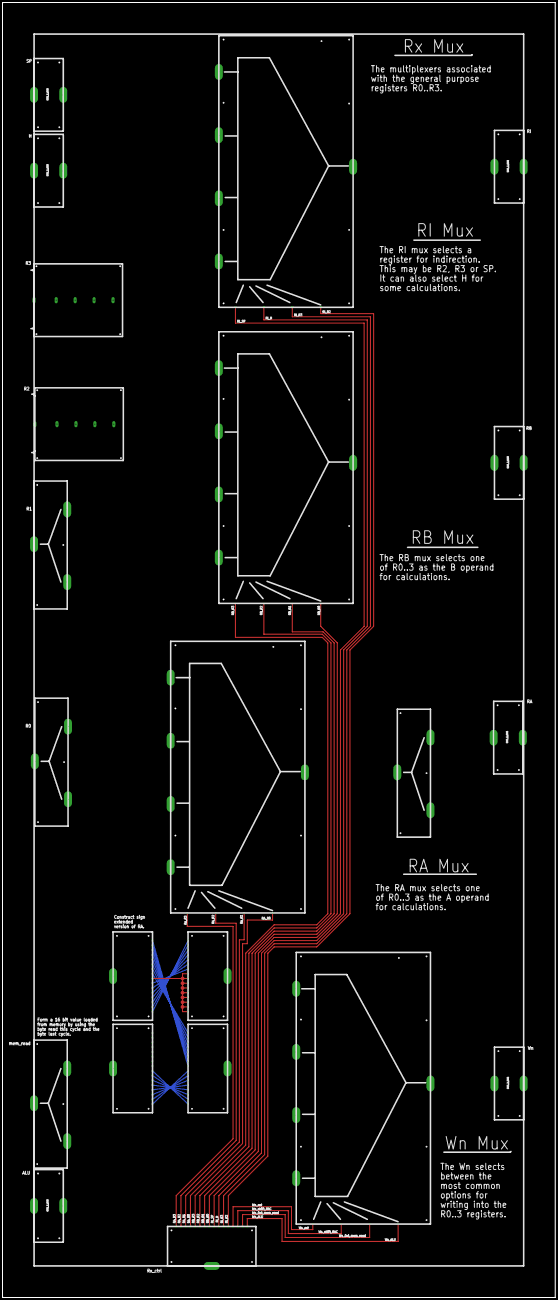
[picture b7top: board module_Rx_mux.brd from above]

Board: 2 copper layers, 444.5 x 1041.4 mm, 22 parts (0 on the bottom side), 63 nets.

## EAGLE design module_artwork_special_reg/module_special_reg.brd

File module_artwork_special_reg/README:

Special Purpose Registers

This is where the processor registers Stack Pointer (SP), Program
Counter (PC) and Helper (H) registers are. In addition the registers
driving the external address bus and write data are here. Most of the
functionality is just multiplexing but there is also an adder provided
to allow the H register count out the number of iterations required for
iterative instructions.

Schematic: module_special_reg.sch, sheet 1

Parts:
CMP9, CMP14: BUS_SPLIT_DISPLAY

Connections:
BUS_SPECIAL_REG_CTRL1: CMP14.INPUT
BUS_SPECIAL_REG_CTRL2: CMP9.INPUT
H_COUNT_DOWN__SHIFT: CMP9.P$1 (OUT_0); also elsewhere on the board
NEXT_ADDR_MUX_ADD2: CMP14.P$9 (OUT_8); also elsewhere on the board
NEXT_ADDR_MUX_PC: CMP14.P$7 (OUT_6); also elsewhere on the board
NEXT_ADDR_MUX_READ_WORD: CMP14.P$8 (OUT_7); also elsewhere on the board
NEXT_ADDR_MUX_RI: CMP14.P$10 (OUT_9); also elsewhere on the board
NEXT_H_MUX_A_ABS_MSB: CMP9.P$11 (OUT_10); also elsewhere on the board
NEXT_H_MUX_A_ADD2: CMP9.P$12 (OUT_11); also elsewhere on the board
NEXT_H_MUX_A_R1: CMP9.P$10 (OUT_9); also elsewhere on the board
NEXT_H_MUX_A_SXT_RD_DATA: CMP9.P$9 (OUT_8); also elsewhere on the board
NEXT_H_MUX_B_A: CMP9.P$3 (OUT_2); also elsewhere on the board
NEXT_H_MUX_B_HOLD: CMP9.P$2 (OUT_1); also elsewhere on the board
NEXT_H_MUX_B_SHIFT_REG_VAL: CMP9.P$4 (OUT_3); also elsewhere on the board
NEXT_H_MUX_B_SHIFT_UPDATE: CMP9.P$5 (OUT_4); also elsewhere on the board
NEXT_PC_MUX_ADD2: CMP14.P$5 (OUT_4); also elsewhere on the board
NEXT_PC_MUX_HOLD: CMP14.P$3 (OUT_2); also elsewhere on the board
NEXT_PC_MUX_H_AND_DATA: CMP14.P$4 (OUT_3); also elsewhere on the board
NEXT_SP_MUX_ADD2: CMP14.P$11 (OUT_10); also elsewhere on the board
NEXT_SP_MUX_HOLD: CMP14.P$12 (OUT_11); also elsewhere on the board
NEXT_WR_DATA_MUX_PC_RA_LSB: CMP9.P$7 (OUT_6); also elsewhere on the board
NEXT_WR_DATA_MUX_PC_RA_MSB: CMP9.P$8 (OUT_7); also elsewhere on the board
NEXT_WR_DATA_MUX_PS: CMP9.P$6 (OUT_5); also elsewhere on the board
NEXT_WR_DATA_WIDE_MUX_PC: CMP9.P$13 (OUT_12); also elsewhere on the board
NEXT_WR_DATA_WIDE_MUX_RA: CMP9.P$14 (OUT_13); also elsewhere on the board
OPCODE_IS_STACK_REL_GROUP_N: CMP9.P$15 (OUT_14); also elsewhere on the board
TRAP_STATE_7: CMP14.P$6 (OUT_5); also elsewhere on the board
VECTOR_CODE_0: CMP14.P$2 (OUT_1); also elsewhere on the board
VECTOR_CODE_1: CMP14.P$1 (OUT_0); also elsewhere on the board

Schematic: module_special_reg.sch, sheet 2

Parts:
CMP19, CMP21, CMP22: BUS_SPLIT_DISPLAY

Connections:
BUS_H_ADDER: CMP22.INPUT; also elsewhere on the board
BUS_H_D: CMP19.INPUT; also elsewhere on the board
BUS_ZERO_EXTEND_READ_DATA: CMP21.INPUT
H_0: CMP19.P$1 (OUT_0)
H_1: CMP19.P$2 (OUT_1)
H_2: CMP19.P$3 (OUT_2)
H_3: CMP19.P$4 (OUT_3)
H_4: CMP19.P$5 (OUT_4)
H_5: CMP19.P$6 (OUT_5); also elsewhere on the board
H_6: CMP19.P$7 (OUT_6); also elsewhere on the board
H_7: CMP19.P$8 (OUT_7); also elsewhere on the board
H_8: CMP19.P$9 (OUT_8)
H_9: CMP19.P$10 (OUT_9)
H_10: CMP19.P$11 (OUT_10)
H_11: CMP19.P$12 (OUT_11)
H_12: CMP19.P$13 (OUT_12)
H_13: CMP19.P$14 (OUT_13)
H_14: CMP19.P$15 (OUT_14)
H_15: CMP19.P$16 (OUT_15)
H_ADDER0: CMP22.P$1 (OUT_0); also elsewhere on the board
H_ADDER1: CMP22.P$2 (OUT_1); also elsewhere on the board
H_ADDER2: CMP22.P$3 (OUT_2); also elsewhere on the board
H_ADDER3: CMP22.P$4 (OUT_3); also elsewhere on the board
H_ADDER4: CMP22.P$5 (OUT_4); also elsewhere on the board
H_ADDER5: CMP22.P$6 (OUT_5)
H_ADDER6: CMP22.P$7 (OUT_6)
H_ADDER7: CMP22.P$8 (OUT_7)
H_ADDER8: CMP22.P$9 (OUT_8)
H_ADDER9: CMP22.P$10 (OUT_9)
H_ADDER10: CMP22.P$11 (OUT_10)
H_ADDER11: CMP22.P$12 (OUT_11)
H_ADDER12: CMP22.P$13 (OUT_12)
H_ADDER13: CMP22.P$14 (OUT_13)
H_ADDER14: CMP22.P$15 (OUT_14)
H_ADDER15: CMP22.P$16 (OUT_15)
ZXT_READ_DATA_0: CMP21.P$1 (OUT_0); also elsewhere on the board
ZXT_READ_DATA_1: CMP21.P$2 (OUT_1); also elsewhere on the board
ZXT_READ_DATA_2: CMP21.P$3 (OUT_2); also elsewhere on the board
ZXT_READ_DATA_3: CMP21.P$4 (OUT_3); also elsewhere on the board
ZXT_READ_DATA_4: CMP21.P$5 (OUT_4); also elsewhere on the board
ZXT_READ_DATA_5: CMP21.P$6 (OUT_5); also elsewhere on the board
ZXT_READ_DATA_6: CMP21.P$7 (OUT_6); also elsewhere on the board
ZXT_READ_DATA_7: CMP21.P$8 (OUT_7); also elsewhere on the board
ZXT_READ_DATA_8: CMP21.P$9 (OUT_8)
ZXT_READ_DATA_9: CMP21.P$10 (OUT_9)
ZXT_READ_DATA_10: CMP21.P$11 (OUT_10)
ZXT_READ_DATA_11: CMP21.P$12 (OUT_11)
ZXT_READ_DATA_12: CMP21.P$13 (OUT_12)
ZXT_READ_DATA_13: CMP21.P$14 (OUT_13)
ZXT_READ_DATA_14: CMP21.P$15 (OUT_14)
ZXT_READ_DATA_15: CMP21.P$16 (OUT_15)

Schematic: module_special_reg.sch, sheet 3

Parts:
CMP5, CMP25, CMP26, CMP48: BUS_2_BUS; BUS2BUS
CMP10, CMP11: BUS_4TEE
CMP16: BUS_TEE
CMP17: BUS_SPLIT_DISPLAY

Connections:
ADD2_0: CMP17.P$1 (OUT_0); also elsewhere on the board
ADD2_1: CMP17.P$2 (OUT_1); also elsewhere on the board
ADD2_2: CMP17.P$3 (OUT_2); also elsewhere on the board
ADD2_3: CMP17.P$4 (OUT_3); also elsewhere on the board
ADD2_4: CMP17.P$5 (OUT_4); also elsewhere on the board
ADD2_5: CMP17.P$6 (OUT_5); also elsewhere on the board
ADD2_6: CMP17.P$7 (OUT_6); also elsewhere on the board
ADD2_7: CMP17.P$8 (OUT_7); also elsewhere on the board
BUS_ADD2_A: CMP10.2; also elsewhere on the board
BUS_ADD2_B: CMP10.3; also elsewhere on the board
BUS_ADD2_C: CMP10.4; also elsewhere on the board
BUS_ADD2_D: CMP16.OUT_A (A); also elsewhere on the board
BUS_MEMORY_READ_WORD: CMP11.SRC
BUS_MEMORY_READ_WORD_A: CMP11.3; also elsewhere on the board
BUS_MEMORY_READ_WORD_B: CMP11.4; also elsewhere on the board
BUS_MEMORY_READ_WORD_C: CMP11.2; also elsewhere on the board
BUS_MEMORY_READ_WORD_D: CMP11.1
BUS_PS: CMP26.P$2 (OUT); also elsewhere on the board
BUS_RA: CMP25.P$2 (OUT); also elsewhere on the board
BUS_RI: CMP48.P$2 (OUT); also elsewhere on the board
unnamed: CMP16.OUTB (B), CMP17.INPUT
unnamed: CMP10.1, CMP16.INPUT (IN)
REG_R1_ROTATE: CMP5.P$2 (OUT); also elsewhere on the board

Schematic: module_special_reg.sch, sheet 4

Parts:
CMP1, CMP2: 4X16MUX
CMP3, CMP32: BUS_2_BUS; BUS2BUS
CMP33: BUS_TEE
CMP34: BUS_4TEE
CMP41: 16REG
CMP43: 4DIGIT
U$1: BYTE_WORD; WORD_BYTE

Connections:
BUS_ADD2_D: CMP1.PORT0; also elsewhere on the board
BUS_H_A: CMP33.INPUT (IN), CMP34.1
BUS_H_B: CMP34.2; also elsewhere on the board
BUS_H_C: CMP2.PORT3, CMP34.4
BUS_H_D: CMP34.3; also elsewhere on the board
BUS_MEMORY_READ_WORD_C: CMP1.PORT1; also elsewhere on the board
DISP_CONN: CMP41.DISPLAY (DSP), CMP43.P$1
H_MSB: CMP32.P$1 (IN), U$1.MSB_1
H_OUT: CMP3.P$1 (IN), CMP33.OUT_A (A)
H_SHIFT_UPDATE_DATA: CMP2.PORT1; also elsewhere on the board
unnamed: CMP33.OUTB (B), U$1.SRC (WORD)
NEXT_H_MUX: CMP2.PORTOUT (OUTPUT), CMP41.INPUT (IN)
NEXT_H_MUX_A: CMP1.PORTOUT (OUTPUT), CMP2.PORT2
NEXT_H_MUX_A_ABS_MSB: CMP1.EN1; also elsewhere on the board
NEXT_H_MUX_A_ADD2: CMP1.EN0; also elsewhere on the board
NEXT_H_MUX_A_R1: CMP1.EN2; also elsewhere on the board
NEXT_H_MUX_A_SXT_RD_DATA: CMP1.EN3; also elsewhere on the board
NEXT_H_MUX_B_A: CMP2.EN2; also elsewhere on the board
NEXT_H_MUX_B_HOLD: CMP2.EN3; also elsewhere on the board
NEXT_H_MUX_B_SHIFT_REG_VAL: CMP2.EN0; also elsewhere on the board
NEXT_H_MUX_B_SHIFT_UPDATE: CMP2.EN1; also elsewhere on the board
REG_H: CMP34.SRC, CMP41.OUT
REG_R1_ROTATE: CMP1.PORT2; also elsewhere on the board
SHIFT_REG_VALUE: CMP2.PORT0; also elsewhere on the board
SIGN_EXTEND_READ_DATA: CMP1.PORT3; also elsewhere on the board

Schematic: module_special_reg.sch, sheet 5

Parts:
CMP4: BUS_CONSTRUCT; BUS_SPLIT
CMP6: 8BIT_ADD_SUB
CMP7: 3X2DIGIT

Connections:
BUS_H_ADDER: CMP6.R; also elsewhere on the board
BUS_H_B: CMP6.A; also elsewhere on the board
H_COUNT_DOWN__SHIFT: CMP6.C_IN, CMP6.INV_B; also elsewhere on the board
unnamed: CMP4.INPUT (OUT), CMP6.B
unnamed: CMP4.P$2 (IN_1), CMP4.P$3 (IN_2), CMP4.P$4 (IN_3), CMP4.P$5 (IN_4), CMP4.P$6 (IN_5), CMP4.P$7 (IN_6), CMP4.P$8 (IN_7), CMP4.P$9 (IN_8), CMP4.P$10 (IN_9), CMP4.P$11 (IN_10), CMP4.P$12 (IN_11), CMP4.P$13 (IN_12), CMP4.P$14 (IN_13), CMP4.P$15 (IN_14), CMP4.P$16 (IN_15)
unnamed: CMP6.DISP, CMP7.P$1
